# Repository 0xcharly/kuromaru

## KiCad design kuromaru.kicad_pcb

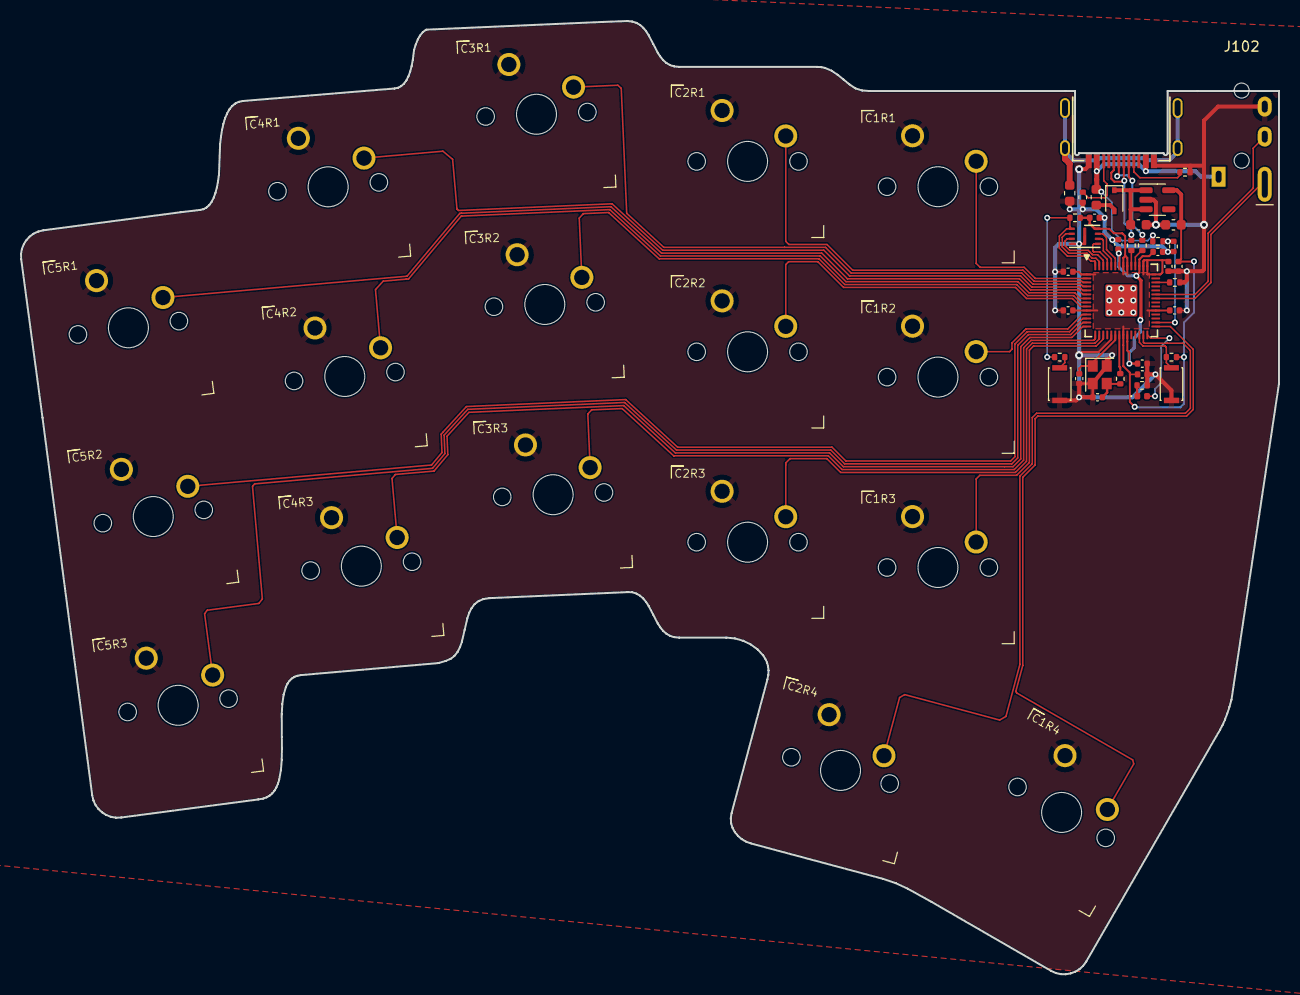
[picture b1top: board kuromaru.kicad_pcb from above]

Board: 2 copper layers, 125.5 x 95.1 mm, 55 parts (0 on the bottom side), 47 nets.

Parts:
C1, C2: 1µ; C_0603_1608Metric
C1R1, C1R2, C1R3, C2R1, C2R2, C2R3, C2R4, C3R1, C3R2, C3R3, C4R1, C4R2, C4R3, C5R1, C5R2, C5R3: SW_Push_SK6812; delay_SW_MX_flipped
C1R4: locked; delay_SW_MX_flipped
C3, C4: 15p; C_0402_1005Metric
C5, C6: 1µ; C_0402_1005Metric
C7, C8, C9, C10, C11, C12, C13, C14: 100n; C_0402_1005Metric
D1: LED; LED_0402_1005Metric
D2: B5817; D_SOD-323
F1: Polyfuse; Fuse_0603_1608Metric
FB1: FerriteBead_Small; L_0603_1608Metric
J1: USB_C_Receptacle_USB2.0; USB_C_Receptacle_HRO_TYPE-C-31-M-13B
J102: Serial; delay_TRRS_PJ_320A
R1, R3, R8: 1k; R_0402_1005Metric
R2, R9, R11: 10k; R_0402_1005Metric
R4, R5, R10: 5.1k; R_0402_1005Metric
R6, R7: 27; R_0402_1005Metric
R14: 5.1k; R_0402_1005Metric_nolabel
SW1, SW2: SW_Push; SW_SPST_CK_KXT3
U1: RP2040; QFN-56-1EP_7x7mm_P0.4mm_EP3.2x3.2mm
U2: GD25Q80CEIGR; USON-8-1EP_3x2mm_P0.5mm_EP0.25x1.65mm
U3: XC6210B332MR-G; SOT-23-5
Y1: Crystal_GND24; Crystal_SMD_2520-4Pin_2.5x2.0mm

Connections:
+1V1: C6.1, C7.1, C8.1, U1.23 (DVDD), U1.45 (VREG_VOUT), U1.50 (DVDD)
+3V3: C2.1, C5.1, C9.1, C10.1, C11.1, C12.1, C13.1, C14.1, R2.2, R9.2, U1.1 (IOVDD), U1.10 (IOVDD), U1.22 (IOVDD), U1.33 (IOVDD), U1.42 (IOVDD), U1.43 (ADC_AVDD), U1.44 (VREG_IN), U1.48 (USB_VDD), U1.49 (IOVDD), U2.8 (VCC), U3.5 (VOUT)
+5V: C1.1, D2.1 (K), U3.1 (VIN), U3.3 (EN)
/D+: J1.A6 (D+), J1.B6 (D+), R6.1
/D-: J1.A7 (D-), J1.B7 (D-), R7.1
/LED: D1.2 (A), U1.28 (GPIO17)
/QSPI_D0: U1.53 (QSPI_SD0), U2.5 (DI(IO0))
/QSPI_D1: U1.55 (QSPI_SD1), U2.2 (DO(IO1))
/QSPI_D2: U1.54 (QSPI_SD2), U2.3 (IO2)
/QSPI_D3: U1.51 (QSPI_SD3), U2.7 (IO3)
/QSPI_SCLK: U1.52 (QSPI_SCLK), U2.6 (CLK)
/QSPI_~CS: R3.2, R9.1, U1.56 (QSPI_SS), U2.1 (~CS)
/VBUS_DET: R10.1, R11.2, U1.30 (GPIO19)
GND: C1.2, C1R1.1, C1R2.1, C1R3.1, C1R4.1, C2.2, C2R1.1, C2R2.1, C2R3.1, C2R4.1, C3.2, C3R1.1, C3R2.1, C3R3.1, C4.2, C4R1.1, C4R2.1, C4R3.1, C5.2, C5R1.1, C5R2.1, C5R3.1, C6.2, C7.2, C8.2, C9.2, C10.2, C11.2, C12.2, C13.2, C14.2, FB1.1, J1.A1 (GND), J1.A12 (GND), J1.B1 (GND), J1.B12 (GND), J102.T, R1.1, R4.1, R5.1, R11.1, R14.2, SW1.1, SW2.1, U1.19 (TESTEN), U1.57 (GND), U2.4 (GND), U2.9 (EP), U3.2 (GND), Y1.2, Y1.4
unnamed: C3.1, U1.20 (XIN), Y1.1
unnamed: C4.1, R8.1, Y1.3
unnamed: D1.1 (K), R1.2
unnamed: D2.2 (A), F1.2
unnamed: FB1.2, J1.S1 (SHIELD)
unnamed: J1.A5 (CC1), R4.2
unnamed: J1.B5 (CC2), R5.2
unnamed: R3.1, SW2.2
unnamed: R6.2, U1.47 (USB_DP)
unnamed: R7.2, U1.46 (USB_DM)
unnamed: R8.2, U1.21 (XOUT)
VBUS: F1.1, J1.A4 (VBUS), J1.A9 (VBUS), J1.B4 (VBUS), J1.B9 (VBUS), J102.S, R10.2
hands: R14.1, U1.40 (GPIO28_ADC2)
reset: R2.1, SW1.2, U1.26 (RUN/~RST)
serial_rx: J102.R1, U1.37 (GPIO25)
serial_tx: J102.R2, U1.36 (GPIO24)
switch_c1r1: C1R1.2, U1.2 (GPIO0)
switch_c1r2: C1R2.2, U1.11 (GPIO8)
switch_c1r3: C1R3.2, U1.17 (GPIO14)
switch_c1r4: C1R4.2, U1.29 (GPIO18)
switch_c2r1: C2R1.2, U1.3 (GPIO1)
switch_c2r2: C2R2.2, U1.9 (GPIO7)
switch_c2r3: C2R3.2, U1.16 (GPIO13)
switch_c2r4: C2R4.2, U1.27 (GPIO16)
switch_c3r1: C3R1.2, U1.4 (GPIO2)
switch_c3r2: C3R2.2, U1.8 (GPIO6)
switch_c3r3: C3R3.2, U1.15 (GPIO12)
switch_c4r1: C4R1.2, U1.5 (GPIO3)
switch_c4r2: C4R2.2, U1.7 (GPIO5)
switch_c4r3: C4R3.2, U1.14 (GPIO11)
switch_c5r1: C5R1.2, U1.6 (GPIO4)
switch_c5r2: C5R2.2, U1.12 (GPIO9)
switch_c5r3: C5R3.2, U1.13 (GPIO10)

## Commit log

2022-08-26 Before diodeless design
2022-08-29 Update to diodeless
2022-09-01 Rework controller, commit before splay
2022-09-01 Post splay
2022-09-02 Before messing around with orientation
2022-09-03 Some reroute with better orientation
2022-09-04 Fix a few violations
2022-09-04 Clean reroute of the thumb cluster
2022-09-04 More route cleanup
2022-09-04 Fix serial connector
2022-09-08 Make thumb 1.5u
2022-09-10 Remove RGB
2022-09-10 Ready for order
2022-09-11 Update USB-C port to use M14
